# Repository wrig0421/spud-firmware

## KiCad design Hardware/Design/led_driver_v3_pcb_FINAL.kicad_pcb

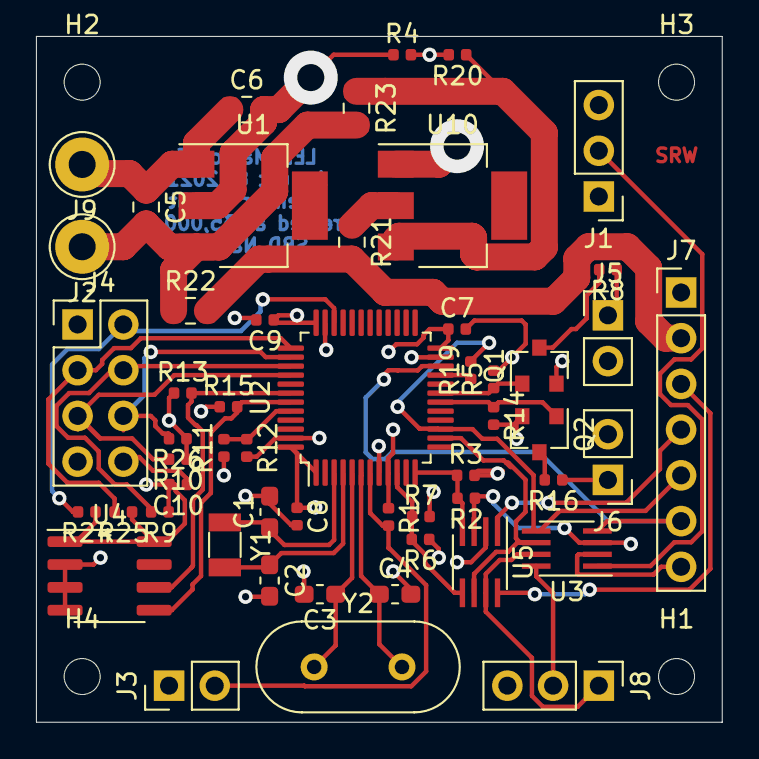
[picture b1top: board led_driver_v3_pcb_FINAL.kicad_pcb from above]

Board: 4 copper layers, 38.1 x 38.1 mm, 57 parts (0 on the bottom side), 35 nets.

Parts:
C1, C2, C3, C4: CP1_Small; C_0603_1608Metric_Pad1.05x0.95mm_HandSolder
C5, C6: 10u; C_0805_2012Metric
C7, C8, C9, C10: 1u; C_0402_1005Metric
H1, H2, H3, H4: MountingHole_Pad; MountingHole_2mm
J1, J8: Conn_01x03_Male; PinHeader_1x03_P2.54mm_Vertical
J2, J9: Conn_01x01_Male; Pin_D1.3mm_L11.0mm_LooseFit
J3, J5, J6: Conn_01x02_Male; PinHeader_1x02_P2.54mm_Vertical
J4: Conn_01x08_Male; PinHeader_2x04_P2.54mm_Vertical
J7: Conn_01x07_Male; PinHeader_1x07_P2.54mm_Vertical
Q1, Q2: BSS138; SOT-23
R1, R2, R6, R9, R10, R12, R13, R15, R24, R25, R26: 10k; R_0402_1005Metric
R3, R7, R11, R19: DNI; R_0402_1005Metric
R4, R5, R14, R20: 1M; R_0402_1005Metric
R8, R16: 100; R_0402_1005Metric
R21, R22: 0; R_0805_2012Metric
R23: DNI; R_0805_2012Metric
U1, U10: TLV1117-33; SOT-223
U2: STM32L433CCTx; LQFP-48_7x7mm_P0.5mm
U3, U5: TXS0102DCT; SSOP-8_2.95x2.8mm_P0.65mm
U4: CAT24C256; SOIC-8_3.9x4.9mm_P1.27mm
Y1: 32.768k Crystal; Crystal_SMD_3215-2Pin_3.2x1.5mm
Y2: 8M; Crystal_HC49-U_Vertical

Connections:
+3V3: C6.2, C7.1, C8.1, C9.1, C10.2, J4.1, R1.1, R2.1, R4.1, R6.1, R9.1, R10.1, R11.1, R13.1, R15.1, R24.1, R25.1, R26.1, U1.2, U2.1, U2.9, U2.24, U2.36, U2.48, U3.3, U4.1, U4.8, U5.3
/12V_EN: R20.1, R23.1, U10.3
/GRN_LED: Q1.1, R5.1, U2.19
/I2C1_SCL: R13.2, U2.42, U4.6
/I2C1_SDA: R15.2, U2.43, U4.5
/INT2: R6.2, R7.1, U2.10, U5.5
/INT2_5V: J7.3, U5.8
/INT3: R2.2, R3.1, U2.12, U5.4
/INT3_5V: J7.4, U5.1
/LED_STRIP_OUT_1: J8.2, U3.8
/LED_STRIP_OUT_2: J1.2, U3.1
/LVL_SHIFTER_EN: U2.14, U3.6, U5.6
/NJTRST: J4.5, R10.2, U2.40
/RED_LED: Q2.1, R14.1, U2.18
/RST: J3.2, R1.2, U2.7
/STM32_LED_STRIP_OUT_1: J7.5, R19.2, U2.15, U3.5
/STM32_LED_STRIP_OUT_2: J7.6, U2.22, U3.4
/STM32_LED_STRIP_OUT_BACKUP: R19.1, U2.21
/SWCLK: J4.3, R25.2, U2.37
/SWDIO: J4.2, R24.2, U2.34
/SWO: J4.4, R9.2, U2.39
/SYS_5V: J1.1, J5.2, J6.2, J7.2, J8.1, R21.2, R22.2, U3.7, U5.7
/TDI: J4.6, R26.2, U2.38
/VIN: C5.2, J2.1, R22.1, R23.2, U1.3
/XTAL1: C1.1, U2.3, Y1.2
/XTAL1_HI: C3.1, U2.5, Y2.1
/XTAL2: C2.1, U2.4, Y1.1
/XTAL2_HI: C4.1, U2.6, Y2.2
GND: C1.2, C2.2, C3.2, C4.2, C5.1, C6.1, C7.2, C8.2, C9.2, C10.1, J1.3, J3.1, J4.8, J7.1, J7.7, J8.3, J9.1, Q1.2, Q2.2, R3.2, R4.2, R5.2, R7.2, R12.2, R14.2, R20.2, U1.1, U2.8, U2.23, U2.35, U2.47, U3.2, U4.2, U4.3, U4.4, U5.2, U10.1
unnamed: J5.1, R8.1
unnamed: J6.1, R16.1
unnamed: Q1.3, R8.2
unnamed: Q2.3, R16.2
unnamed: R11.2, R12.1, U2.44
unnamed: R21.1, U10.2
